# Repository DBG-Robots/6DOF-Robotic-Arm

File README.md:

# 6DOF Robotic Arm

A 6 degree-of-freedom robotic arm built from scratch. The project covers the full hardware and software stack: a custom STM32-based motor controller PCB, 3D-printed mechanical structure, and embedded firmware.

---

## Project Status

| Area | Status |
|---|---|
| Schematic | Complete |
| PCB Layout | In progress |
| STM32CubeMX pin assignment | Complete |
| Firmware | Not started |
| 3D Design | Not started |

---

## Repository Structure

```
.
├── LICENSE
├── PCB/
│   ├── Arm_Controller.kicad_sch       # Top-level schematic
│   ├── MCU.kicad_sch                  # STM32G431CBT6 schematic sheet
│   ├── Drivers.kicad_sch              # TMC2209 driver schematic sheet
│   ├── Power.kicad_sch                # Power supply schematic sheet
│   ├── Connectors.kicad_sch           # Connector schematic sheet
│   ├── Indicator.kicad_sch            # LED indicator schematic sheet
│   ├── Arm_Controller.kicad_pcb       # PCB layout
│   ├── Arm_Controller.kicad_pro       # KiCad project file
│   └── hardware/                      # Datasheets and reference material
└── STM32Cube/
    ├── Core/                          # Generated HAL application code
    ├── Drivers/                       # STM32 HAL and CMSIS drivers
    ├── EWARM/                         # IAR project files
    └── Robot Arm.ioc                  # STM32CubeMX configuration
```

---

## Hardware Overview

### Microcontroller — STM32G431CBT6

The board is centred around an STM32G431CBT6 in LQFP48 packaging, running at 170 MHz via PLL sourced from an 8 MHz external HSE crystal. USB uses the internal HSI48 oscillator via the CK48 mux to hit exactly 48 MHz without pulling the main PLL.

Flash latency is configured to `FLASH_LATENCY_4` as required at 170 MHz. The HAL timebase is moved from SysTick to TIM6 to avoid conflict with the USB stack.

SWD debug is available on PA13 (SWDIO) and PA14 (SWCLK).

### Stepper Motor Drivers — TMC2209

Six TMC2209 drivers handle the six stepper motor axes. Drivers are split into two banks of three, each sharing a UART line for configuration:

- **USART1 (PA9)** — Motors 1–3, half-duplex, 115200 baud
- **USART2 (PB3)** — Motors 4–6, half-duplex, 115200 baud

Up to three drivers share a single UART line using the TMC2209 address selection scheme via MS1/MS2 pins (addresses 0–3).

Each driver exposes a STEP input driven by hardware PWM (TIM2/TIM3 channels), a DIR GPIO, and a shared active-low enable line per bank (TMC_A_ENN, TMC_B_ENN). DIAG outputs from all six drivers are wired to EXTI lines 10–15 on PORTB for simultaneous independent fault interrupts.

Motor output pins (A1, A2, B1, B2 per driver) connect to 5 mm pitch screw terminals for direct stepper wiring.

Sense resistors are 0.11 Ω in 1206 package. Sustained motor current must not exceed 1.5 A per driver to stay within the 0.25 W resistor rating.

The TMC2209 accepts 4.75 V to 29 V on its motor supply. The 24 V rail is protected by a TVS diode clamping at ~29 V to keep transient spikes within this limit, particularly relevant when running from a 6S LiPo (max 25.2 V fully charged).

#### SPREAD Pin Configuration

Each driver has a dedicated 3-way solder jumper (`TMCX_SPREAD`) to select the chopper mode:

| SPREAD state | Mode |
|---|---|
| Pulled LOW (GND) | StealthChop2 — ultra-quiet operation |
| Pulled HIGH (3V3) | SpreadCycle — maximum torque |

Default: pulled HIGH (SpreadCycle). A 100 Ω series resistor is placed between the 3V3 rail and pad 1 of each jumper to limit current in the event of accidental full bridge.

> **Friendly Reminder:** Always have exactly ONE bridge between two pads! Keeping SPREAD floating will result in undefined behaviour and bridging all 3 pads will short GND and +3V3, resulting in a useless piece of green fiberglass. We do not take responsibility for this happening and recommend always testing for a short after resoldering these solder bridges.

### CAN Bus — FDCAN1 with ISO1042DWVR Isolator

CAN communication uses the STM32 FDCAN1 peripheral on PB8 (RX) and PB9 (TX), galvanically isolated via an ISO1042DWVR transceiver. The MCU side runs at 3.3 V; the bus side uses a 5 V isolated supply. Both supply pins carry decoupling capacitors close to the IC.

A 120 Ω termination resistor between CAN_H and CAN_L is present on the bus side, controlled by a solder bridge jumper (JP1). Close JP1 only if this board sits at a physical endpoint of the CAN bus. The default state is open.

> **Note:** JP1 default is OPEN. Exactly two 120 Ω terminations must be present across the entire CAN bus.

The ISO1042 is rated for CAN FD up to 5 Mbps. The board is currently configured for classic CAN. FDCAN timing parameters will need to be recalculated once SYSCLK is confirmed at 170 MHz.

> **TODO:** CAN bus connector footprint is `Connector_Molex:Molex_Pico-Lock_504050-0791_1x07-1MP_P1.50mm_Horizontal`. Exact pinout for the robot-side harness is not yet defined — document and lock this before PCB sign-off.

### Power System

Three 24 V power inputs feed the board via a shared pre-fuse node (`VBAT_IN`), then through a 15 A / 50 V fuse onto the protected `+24V` bus:

- **Robot power distribution board** — dedicated 2-pin connector. Protected by a Schottky diode (MBR1545, SMB package) so no current can ever flow back into the distribution board.
- **Battery** — XT60 female connector on-board, intended for 6S LiPo (22.2 V nominal, 25.2 V max fully charged). Protected by a Schottky diode in the same way.
- **J_PWR24V** — 2-pin 5 mm screw terminal. Accepts a standard 24 V DC supply or any external 24 V source. Also usable as a 24 V output tap. **No diode protection on this connector** — it connects directly to the `VBAT_IN` node ahead of the fuse. Polarity is marked clearly on silkscreen. Reverse polarity here will damage the board.

All three sources meet at `VBAT_IN` before the fuse, so all input current passes through fuse protection regardless of which source is used. Only one power source should be connected at a time.

> **Schottky diode note (MBR1545, D_SMB footprint):** Pin 1 = cathode, pin 2 = anode, pad 3 (thermal tab) = cathode. Pad 3 must be assigned the `VBAT_IN` net in KiCad — it is electrically the cathode and must not be left floating.

#### 24 V Rail Protection

The +24V bus carries decoupling and transient protection split across two locations — one cluster per driver bank — to minimise trace inductance to each group of three TMC2209s:

- A large electrolytic bulk capacitor (1000 µF / 50 V) placed centrally absorbs worst-case transients from all six drivers simultaneously
- Two ceramic capacitors (100 nF / 50 V, 0603) — one per driver bank cluster — handle high-frequency switching noise locally
- Two unidirectional TVS diodes (SMBJ26A) — one per driver bank cluster — clamp transients to protect the TMC2209 drivers, which have a 29 V absolute maximum rating

#### 3.3 V Regulation

Two separate paths supply the 3.3 V rail depending on power source. Both feed through a Schottky diode OR arrangement so neither source can back-feed the other.

**Buck converter (24 V → 3.3 V), used during normal operation:**

Placed in the top-right area of the board, drawing from the +24V bus. The buck converter output is nominally ~3.65 V. With approximately 0.30 V drop across the downstream Schottky diode at typical load, the STM32 VDD rail sits at approximately 3.35 V — within the 2.0 V–3.6 V operating range. The 3.3 V output trace crosses the power plane split boundary on layer 1 to reach the 3V3 plane region under the MCU.

**LDO (USB 5 V → 3.3 V), used during debug/programming only:**

Placed in the bottom-right area alongside the USB-C connector, minimising the VBUS trace length. The LDO output is 3.3 V. With the Schottky drop (~0.30 V at typical load), the STM32 VDD rail sits at approximately 3.0 V — still within the operating range, but marginal. USB power does not supply the motor drivers.

> If exactly 3.3 V is required at the MCU, replace the Schottky diode with an ideal diode circuit, or remove the debug USB power path entirely.

#### 3.3 V Rail Filtering

Given the noisy 24 V environment (6 switching stepper drivers), the 3.3 V rail carries additional filtering beyond a basic dev board:

- A ferrite bead at the rail entry point attenuates noise before it reaches any VDD decoupling
- A bulk reservoir capacitor handles load transients and converter lag
- Three 100 nF ceramics provide per-pin HF decoupling on VDD
- A second, higher-impedance ferrite bead further isolates the VDDA analog supply from VDD
- VDDA carries both a 100 nF and a 1 µF capacitor per ST's reference design
- VREF+ carries a 100 nF decoupling capacitor; a 0 Ω jumper allows VREF+ to be separated from VDDA if needed

### USB

Full-speed USB device on PA11 (DM) and PA12 (DP), clocked from HSI48. Intended for firmware flashing and debug only — does not power the motor drivers. USB-C connector placed bottom-right, adjacent to the LDO.

---

## PCB Layout

### Layer Stack

4-layer board:

| Layer | Use |
|---|---|
| 1 — Top copper | Signal and power routing |
| 2 — GND plane | Unbroken ground reference across the full board |
| 3 — Power plane | Split: 24 V under motor outputs and power section (U-shape), 3V3 under MCU and logic |
| 4 — Bottom copper | Signal routing |

The power plane split boundary runs between the motor-side pads and logic-side pads of each TMC2209 footprint. The GND plane is never split.

### Board Layout

The board follows a U-shaped topology with a central logic section:

- **Top edge** — Motors 4–6: screw terminals facing outward, TMC2209s below with 24 V side facing the edge and logic side facing inward
- **Bottom edge** — Motors 1–3: same orientation mirrored
- **Right-center** — Power input section: XT60 (VBAT), EXTN_PWR connector, J_PWR24V screw terminal, Schottky diodes D1/D2, fuse F1, bulk cap C13, ceramic caps and TVS diodes for each driver bank
- **Top-right** — 24 V → 3.3 V buck converter
- **Bottom-right** — USB-C connector and LDO (5 V → 3.3 V)
- **Center** — STM32G431CBT6, 3.3 V filtering, crystal, decoupling
- **Left edge** — CAN header and isolator (ISO1042DWVR), SWD debug header (J15), expansion headers, LED indicators

### Power Plane Notes

The 24 V plane covers the outer half of the board in a U-shape (top driver bank, power section, bottom driver bank). The 3.3 V plane occupies the inner-right region under the STM32, CAN isolator, and logic components. A copper-free gap separates the two regions; a single GND via stitch bridges them at one point to maintain a common ground reference without creating a loop.

All TMC2209 footprints are oriented so motor output pads (A1, A2, B1, B2) sit over the 24 V plane and logic pads (STEP, DIR, UART, DIAG) sit over the 3.3 V plane. The plane split line runs through the gap between these pad clusters on each driver.

---

## Pin Assignment

### STEP Outputs (Hardware PWM)

| Pin | Label | Timer Channel |
|---|---|---|
| PA0 | TMC1_STEP | TIM2_CH1 |
| PA1 | TMC2_STEP | TIM2_CH2 |
| PA6 | TMC3_STEP | TIM3_CH1 |
| PA7 | TMC4_STEP | TIM3_CH2 |
| PB0 | TMC5_STEP | TIM3_CH3 |
| PB1 | TMC6_STEP | TIM3_CH4 |

TIM2 and TIM3 run independently, allowing different step rates per motor bank.

### DIR Outputs (GPIO)

| Pin | Label |
|---|---|
| PA3 | M1_DIR |
| PA4 | M2_DIR |
| PA5 | M3_DIR |
| PB4 | M4_DIR |
| PB5 | M5_DIR |
| PB6 | M6_DIR |

Grouped by port to allow efficient single-register writes.

### Enable Outputs (Active LOW)

| Pin | Label | Controls |
|---|---|---|
| PA10 | TMC_A_ENN | Motors 1–3 |
| PA15 | TMC_B_ENN | Motors 4–6 |

Pulling both low implements a hardware e-stop across all six axes.

### DIAG Inputs (EXTI)

| Pin | Label | EXTI Line |
|---|---|---|
| PB10 | TMC1_DIAG | EXTI10 |
| PB11 | TMC2_DIAG | EXTI11 |
| PB12 | TMC3_DIAG | EXTI12 |
| PB13 | TMC4_DIAG | EXTI13 |
| PB14 | TMC5_DIAG | EXTI14 |
| PB15 | TMC6_DIAG | EXTI15 |

All DIAG lines sit on unique EXTI lines, so all six can fire simultaneously without arbitration. DIAG is driven HIGH by the TMC2209 on stall or fault detection.

### Indicators

| LED | Pin | Resistor | Color |
|---|---|---|---|
| STATUS_LED | PC13 | 1 kΩ | Red |
| POWER_LED | +3V3 (always-on) | 1.1 kΩ | Green |
| ACTIVITY_LED | PA8 | 390 Ω | Blue |

### Expansion Headers

| Pin | Use |
|---|---|
| PA2 | 3-pin 2.54 mm header (BTN/FAN/Thermistor) |
| PB2 | 3-pin 2.54 mm header (BTN/FAN) |
| PB7 | TIM4_CH2 — recommended for PWM fan control |

Headers are 3-pin 2.54 mm (GND / Signal / 3V3) with 10 kΩ pullup on the signal line for a defined state when unplugged.

PA2 is additionally suitable as a thermistor input (ADC) — the 10 kΩ pullup acts as the upper half of a voltage divider. Standard 10 kΩ NTC thermistors connect between the PA2 signal pad and GND.

---

## BOOT0 / PB8 — nBOOT_SEL Configuration

PB8 is shared between the FDCAN1_RX function and BOOT0. To free PB8 for CAN use permanently, the option byte **nBOOT_SEL = 1** must be programmed via STM32CubeProgrammer at first flash. This redirects boot mode selection away from the physical BOOT0 pin to the nBOOT0 option bit, which is set to 1 (normal boot from flash).

No physical BOOT or RESET button is fitted. NRST is accessible via pin 12 of the SWD header.

A test pad (TP_PB8) is placed on the PCB for two purposes:

1. Probing the CAN receive signal during bring-up.
2. Emergency bootloader recovery on boards where nBOOT_SEL was not programmed correctly — hold TP_PB8 HIGH at power-on to force the ROM bootloader via USB DFU.

---

## SWD Debug Header — J15

- Connector: 2×7 pin, 1.27 mm pitch, vertical through-hole
- KiCad footprint: `Connector_PinHeader_1.27mm:PinHeader_2x07_P1.27mm_Vertical`
- Pinout: STDC14 per ST UM2448 Table 6
- Preferred part: Samtec FTSH-107-01-L-DV-K-A (adds alignment shroud; any 2×7 1.27 mm header is electrically equivalent)
- Recommended debugger: **STLINK-V3MINIE** (ships with STDC14 ribbon cable)

| Pin | Signal |
|---|---|
| 1, 2 | Reserved — NC |
| 3 | T_VCC → +3V3 |
| 4 | SWDIO → PA13 |
| 5, 7 | GND |
| 6 | SWCLK → PA14 |
| 8 | SWO → NC (PB3 occupied by USART2) |
| 9 | NC |
| 10 | NC |
| 11 | GNDDetect → GND |
| 12 | NRST |
| 13, 14 | VCP RX/TX → NC |

---

## Test Points

All test points use 2.0 mm round pads for power rails and 1.0 mm round pads for signals, compatible with flying probe and pogo pin fixtures.

| Signal | Notes |
|---|---|
| GND | Power |
| +3V3 | Power |
| +24V | Power |
| VBUS | Power |
| CC1 | USB |
| CC2 | USB |
| TMC1–6 DIAG | One pad per driver |
| TMC1–6 INDEX | One pad per driver |
| TP_PB8 / BOOT0 | 1.5 mm round pad — CAN RX probe point and bootloader recovery |
| VDDA | Analog supply, after the VDDA ferrite bead |
| VREF+ | ADC reference rail |
| SWDIO | Debug |
| SWDCLK | Debug |
| NRST | Reset |
| CAN_H | Bus signal |
| CAN_L | Bus signal |
| CAN_GND | Bus ground reference |
| CAN_UART_TX | ISO1042 MCU-side TX |
| CAN_UART_RX | ISO1042 MCU-side RX |
| TMC_UART1 | USART1 half-duplex line (motors 1–3) |
| TMC_UART2 | USART2 half-duplex line (motors 4–6) |
| SW_NODE | Buck converter switching node — for scope noise analysis during bring-up |

---

## Known Issues and Open Items

- CAN connector pinout (Molex Pico-Lock 504050-0791) not yet defined for the robot-side harness.
- Connector for robot power distribution board not yet selected — footprint TBD.
- FDCAN timing parameters need recalculation after SYSCLK is confirmed at 170 MHz.
- PCB layout in progress — component placement largely complete, routing not yet started.
- Diode footprints (D1, D2): pad 3 (thermal tab) must be assigned `VBAT_IN` net in KiCad before routing.
- Buck converter and LDO placement pending final placement confirmation.
- Firmware not started.
- 3D mechanical design not started.

---

## Authorship

### 6DOF Robotic Arm — DBG-Robots

**Merlin Ortner**  
**Repository Owner & Principal Maintainer**  
Original author of this repository and responsible for long-term maintenance, development, and stewardship.  
Contact: ortnermerlin@gmail.com

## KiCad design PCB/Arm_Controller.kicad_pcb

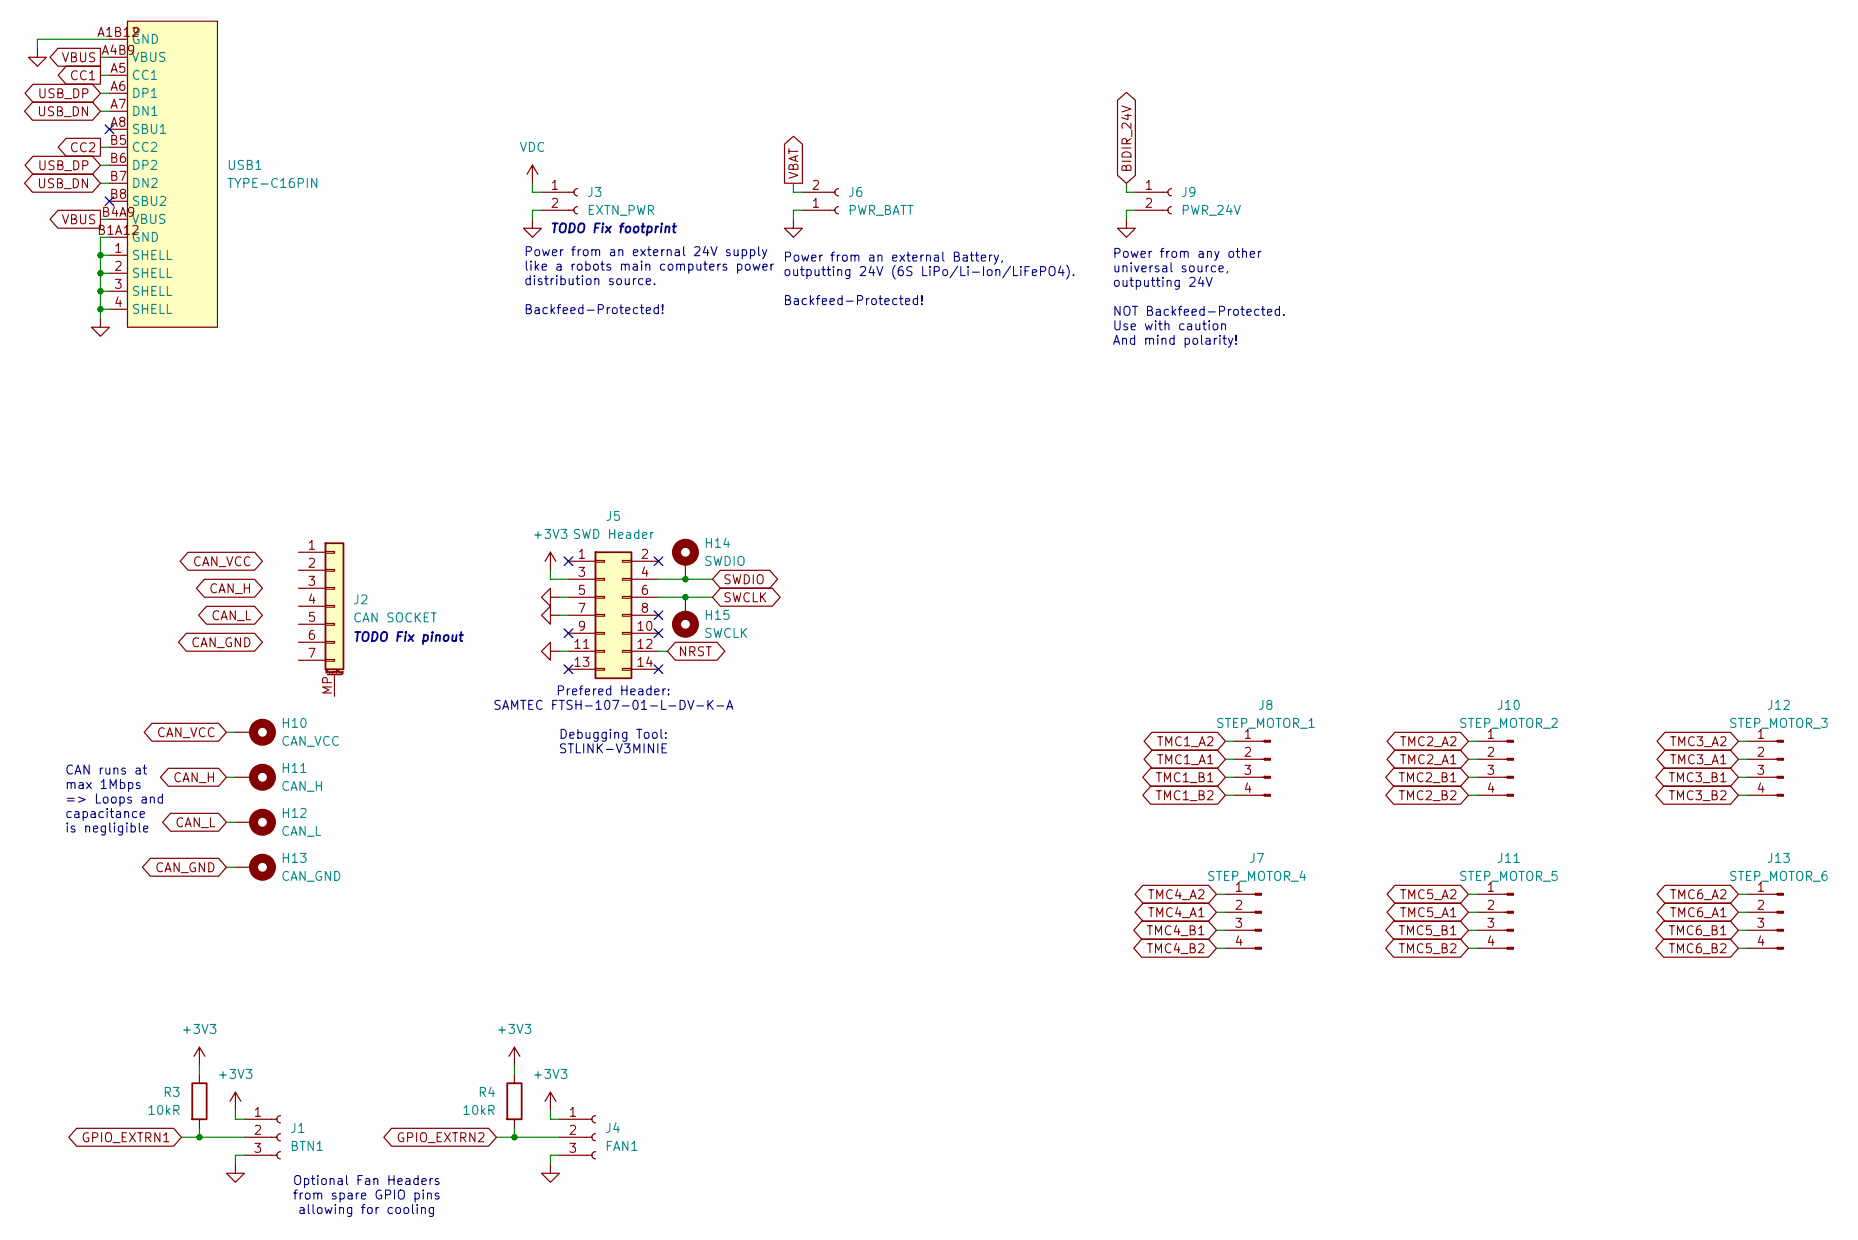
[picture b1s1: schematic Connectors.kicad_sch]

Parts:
H10: CAN_VCC; TestPoint_Pad_D2.0mm
H11: CAN_H; TestPoint_Pad_D1.0mm
H12: CAN_L; TestPoint_Pad_D1.0mm
H13: CAN_GND; TestPoint_Pad_D2.0mm
H14: SWDIO; TestPoint_Pad_D1.0mm
H15: SWCLK; TestPoint_Pad_D1.0mm
J1: BTN1; FanPinHeader_1x03_P2.54mm_Vertical
J2: CAN SOCKET; Molex_Pico-Lock_504050-0791_1x07-1MP_P1.50mm_Horizontal
J3: EXTN_PWR; Molex_SPOX_5267-02A_1x02_P2.50mm_Vertical
J4: FAN1; FanPinHeader_1x03_P2.54mm_Vertical
J5: SWD Header; PinHeader_2x07_P1.27mm_Vertical
J6: PWR_BATT; AMASS_XT60PW-F_1x02_P7.20mm_Horizontal
J7: STEP_MOTOR_4; TerminalBlock_Phoenix_MKDS-1,5-4-5.08_1x04_P5.08mm_Horizont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
J8: STEP_MOTOR_1; TerminalBlock_Phoenix_MKDS-1,5-4-5.08_1x04_P5.08mm_Horizont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
J9: PWR_24V; TerminalBlock_MaiXu_MX126-5.0-02P_1x02_P5.00mm
J10: STEP_MOTOR_2; TerminalBlock_Phoenix_MKDS-1,5-4-5.08_1x04_P5.08mm_Horizont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
J11: STEP_MOTOR_5; TerminalBlock_Phoenix_MKDS-1,5-4-5.08_1x04_P5.08mm_Horizont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
J12: STEP_MOTOR_3; TerminalBlock_Phoenix_MKDS-1,5-4-5.08_1x04_P5.08mm_Horizont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
J13: STEP_MOTOR_6; TerminalBlock_Phoenix_MKDS-1,5-4-5.08_1x04_P5.08mm_Horizont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
R3, R4: 10kR; R_0402_1005Metric
USB1: TYPE-C16PIN; USB-C-SMD_TYPE-C16PIN; MPN TYPE-C16PIN; LCSC Part C393939

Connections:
+3V3: J1.1, J4.1, J5.3, R3.1, R4.1; also elsewhere on the board
BIDIR_24V: J9.1; also elsewhere on the board
CAN_GND: H13.1 (1_1); also elsewhere on the board
CAN_H: H11.1 (1_1); also elsewhere on the board
CAN_L: H12.1 (1_1); also elsewhere on the board
CAN_VCC: H10.1 (1_1); also elsewhere on the board
CC1: USB1.A5 (CC1); also elsewhere on the board
CC2: USB1.B5 (CC2); also elsewhere on the board
GND: J1.3, J3.2, J4.3, J5.5, J5.7, J5.11, J6.1, J9.2, USB1.1 (SHELL), USB1.2 (SHELL), USB1.3 (SHELL), USB1.4 (SHELL), USB1.A1B12 (GND), USB1.B1A12 (GND); also elsewhere on the board
GPIO_EXTRN1: J1.2, R3.2; also elsewhere on the board
GPIO_EXTRN2: J4.2, R4.2; also elsewhere on the board
NRST: J5.12; also elsewhere on the board
SWCLK: H15.1 (1_1), J5.6; also elsewhere on the board
SWDIO: H14.1 (1_1), J5.4; also elsewhere on the board
TMC1_A1: J8.2; also elsewhere on the board
TMC1_A2: J8.1; also elsewhere on the board
TMC1_B1: J8.3; also elsewhere on the board
TMC1_B2: J8.4; also elsewhere on the board
TMC2_A1: J10.2; also elsewhere on the board
TMC2_A2: J10.1; also elsewhere on the board
TMC2_B1: J10.3; also elsewhere on the board
TMC2_B2: J10.4; also elsewhere on the board
TMC3_A1: J12.2; also elsewhere on the board
TMC3_A2: J12.1; also elsewhere on the board
TMC3_B1: J12.3; also elsewhere on the board
TMC3_B2: J12.4; also elsewhere on the board
TMC4_A1: J7.2; also elsewhere on the board
TMC4_A2: J7.1; also elsewhere on the board
TMC4_B1: J7.3; also elsewhere on the board
TMC4_B2: J7.4; also elsewhere on the board
TMC5_A1: J11.2; also elsewhere on the board
TMC5_A2: J11.1; also elsewhere on the board
TMC5_B1: J11.3; also elsewhere on the board
TMC5_B2: J11.4; also elsewhere on the board
TMC6_A1: J13.2; also elsewhere on the board
TMC6_A2: J13.1; also elsewhere on the board
TMC6_B1: J13.3; also elsewhere on the board
TMC6_B2: J13.4; also elsewhere on the board
USB_DN: USB1.A7 (DN1), USB1.B7 (DN2); also elsewhere on the board
USB_DP: USB1.A6 (DP1), USB1.B6 (DP2); also elsewhere on the board
VBAT: J6.2; also elsewhere on the board
VBUS: USB1.A4B9 (VBUS), USB1.B4A9 (VBUS); also elsewhere on the board
VDC: J3.1; also elsewhere on the board

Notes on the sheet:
TODO Fix footprint
Power from an external 24V supply like a robots main computers power distribution source. Backfeed-Protected!
Power from an external Battery, outputting 24V (6S LiPo/Li-Ion/LiFePO4). Backfeed-Protected!
CAN runs at max 1Mbps => Loops and capacitance is negligible
TODO Fix pinout
Prefered Header: SAMTEC FTSH-107-01-L-DV-K-A Debugging Tool: STLINK-V3MINIE
Optional Fan Headers from spare GPIO pins allowing for cooling
Power from any other universal source, outputting 24V NOT Backfeed-Protected. Use with caution And mind polarity!

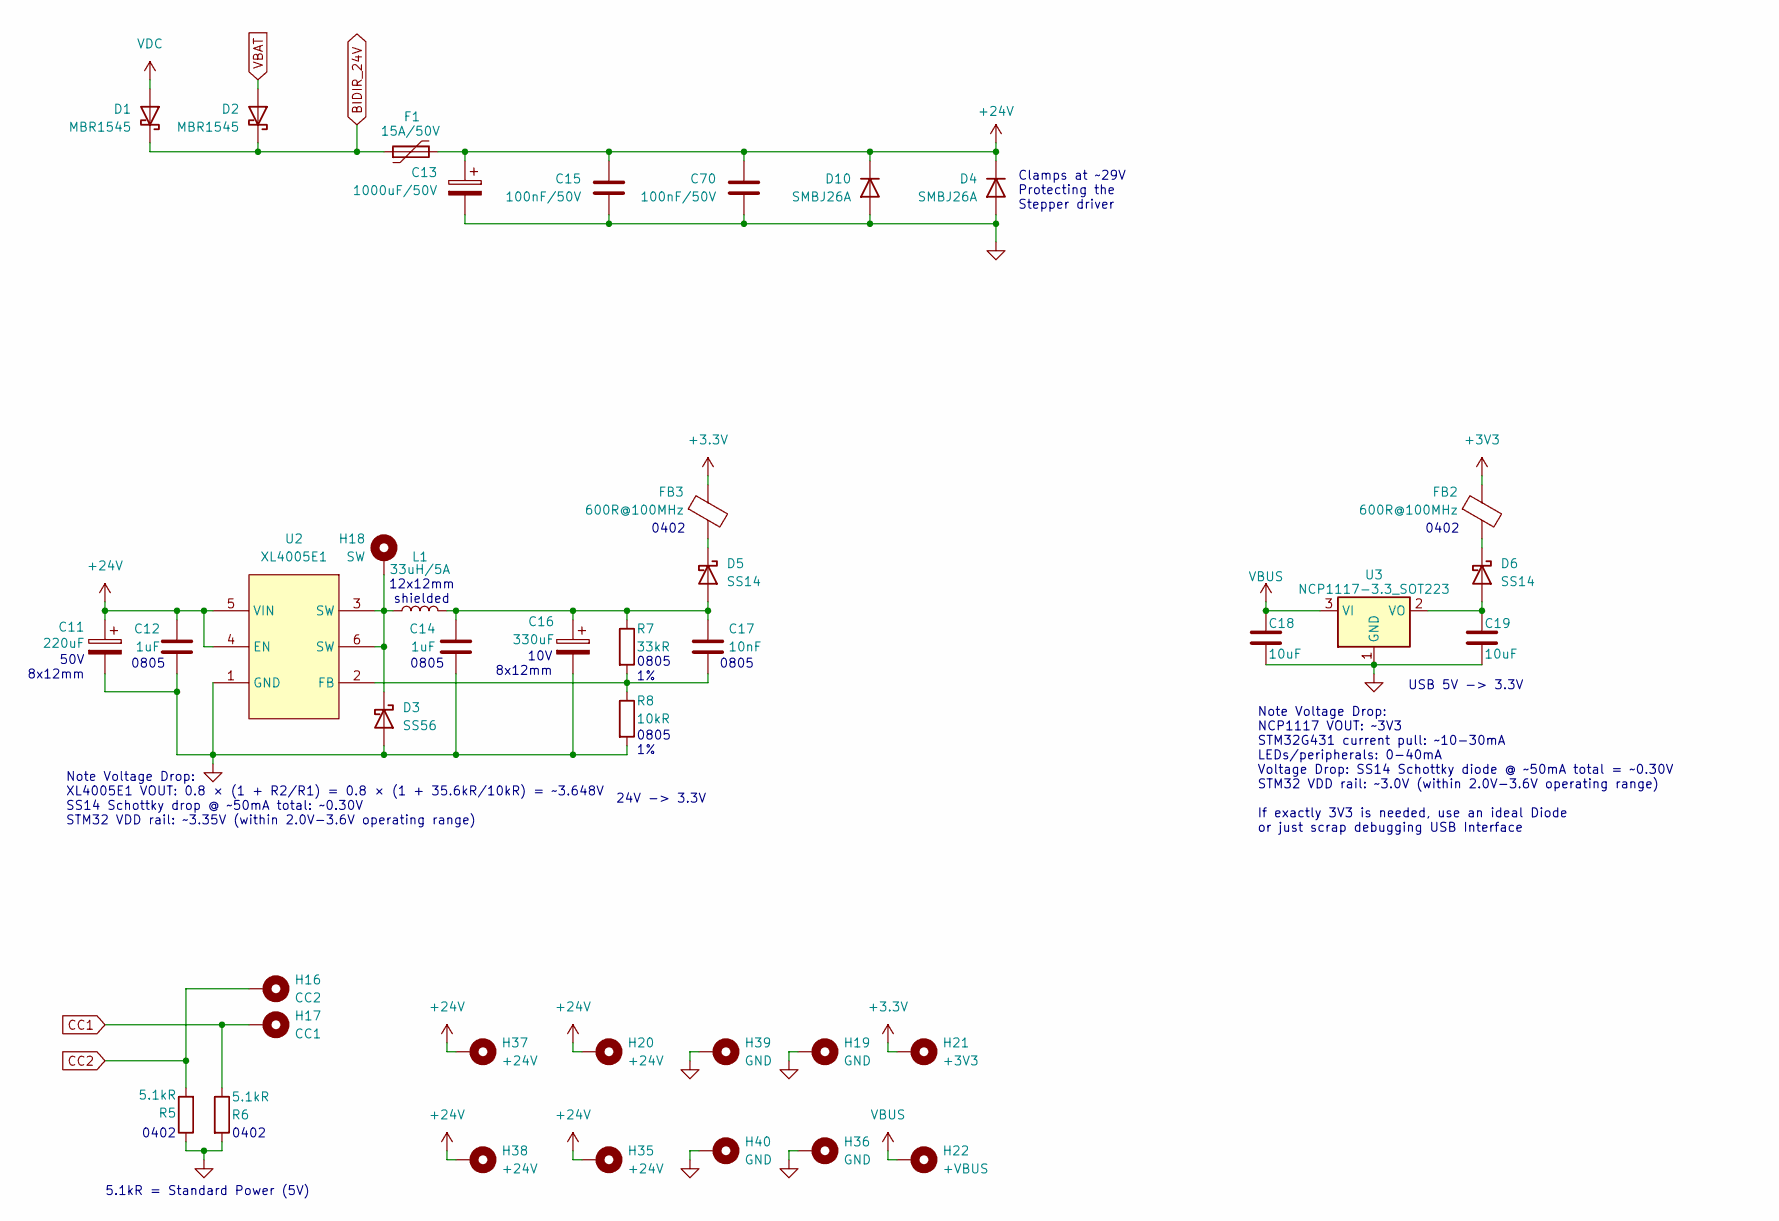
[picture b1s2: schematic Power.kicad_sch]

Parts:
C11: 220uF; CP_Radial_D8.0mm_P3.50mm
C12, C14: 1uF; C_0805_2012Metric
C13: 1000uF/50V; CP_Radial_D10.0mm_P5.00mm
C15, C70: 100nF/50V; C_0603_1608Metric
C16: 330uF; CP_Elec_8x10
C17: 10nF; C_0805_2012Metric
C18, C19: 10uF; C_0805_2012Metric
D1, D2: MBR1545; TO-263-2
D3: SS56; D_SMA
D4, D10: SMBJ26A; D_SMB
D5, D6: SS14; D_SMA
F1: 15A/50V; Fuseholder_Blade_ATO_Littelfuse_Pudenz_2_Pin
FB2, FB3: 600R@100MHz; L_0603_1608Metric
H16: CC2; TestPoint_Pad_D1.0mm
H17: CC1; TestPoint_Pad_D1.0mm
H18: SW; TestPoint_Pad_D1.0mm
H19, H36, H39, H40: GND; TestPoint_Pad_D2.0mm
H20, H35, H37, H38: +24V; TestPoint_Pad_D2.0mm
H21: +3V3; TestPoint_Pad_D2.0mm
H22: +VBUS; TestPoint_Pad_D2.0mm
L1: 33uH/5A; L_Bourns_SRR1260
R5, R6: 5.1kR; R_0402_1005Metric
R7: 33kR; R_0805_2012Metric
R8: 10kR; R_0805_2012Metric
U2: XL4005E1; TO-263-5_L10.2-W9.2-P1.70-TL; MPN XL4005E1; LCSC Part C73332
U3: NCP1117-3.3_SOT223; SOT-223-3_TabPin2

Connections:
+3.3V: FB3.1, H21.1 (1_1); also elsewhere on the board
+3V3: FB2.1; also elsewhere on the board
+24V: C11.1, C12.1, C13.1, C15.1, C70.1, D4.1 (K), D10.1 (K), F1.2, H20.1 (1_1), H35.1 (1_1), H37.1 (1_1), H38.1 (1_1), U2.4 (EN), U2.5 (VIN); also elsewhere on the board
BIDIR_24V: D1.1 (K), D2.1 (K), F1.1; also elsewhere on the board
CC1: H17.1 (1_1), R6.1; also elsewhere on the board
CC2: H16.1 (1_1), R5.2; also elsewhere on the board
GND: C11.2, C12.2, C13.2, C14.2, C15.2, C16.2, C18.2, C19.2, C70.2, D3.2 (A), D4.2 (A), D10.2 (A), H19.1 (1_1), H36.1 (1_1), H39.1 (1_1), H40.1 (1_1), R5.1, R6.2, R8.2, U2.1 (GND), U3.1 (GND); also elsewhere on the board
unnamed: D3.1 (K), H18.1 (1_1), L1.1, U2.3 (SW), U2.6 (SW)
unnamed: C14.1, C16.1, C17.1, D5.2 (A), L1.2, R7.1
unnamed: D5.1 (K), FB3.2
unnamed: C19.1, D6.2 (A), U3.2 (VO)
unnamed: D6.1 (K), FB2.2
unnamed: C17.2, R7.2, R8.1, U2.2 (FB)
VBAT: D2.2 (A); also elsewhere on the board
VBUS: C18.1, H22.1 (1_1), U3.3 (VI); also elsewhere on the board
VDC: D1.2 (A); also elsewhere on the board

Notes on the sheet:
0805
0805 1%
Clamps at ~29V Protecting the Stepper driver
10V 8x12mm
Note Voltage Drop: XL4005E1 VOUT: 0.8 × (1 + R2/R1) = 0.8 × (1 + 35.6kR/10kR) = ~3.648V SS14 Schottky drop @ ~50mA total: ~0.30V STM32 VDD rail: ~3.35V (within 2.0V-3.6V operating range)
USB 5V -> 3.3V
24V -> 3.3V
Note Voltage Drop: NCP1117 VOUT: ~3V3 STM32G431 current pull: ~10-30mA LEDs/peripherals: 0-40mA Voltage Drop: SS14 Schottky diode @ ~50mA total = ~0.30V STM32 VDD rail: ~3.0V (within 2.0V-3.6V operating range) If exactly 3V3 is needed, use an ideal Diode or just scrap debugging USB Interface
50V 8x12mm
5.1kR = Standard Power (5V)
0402
12x12mm shielded

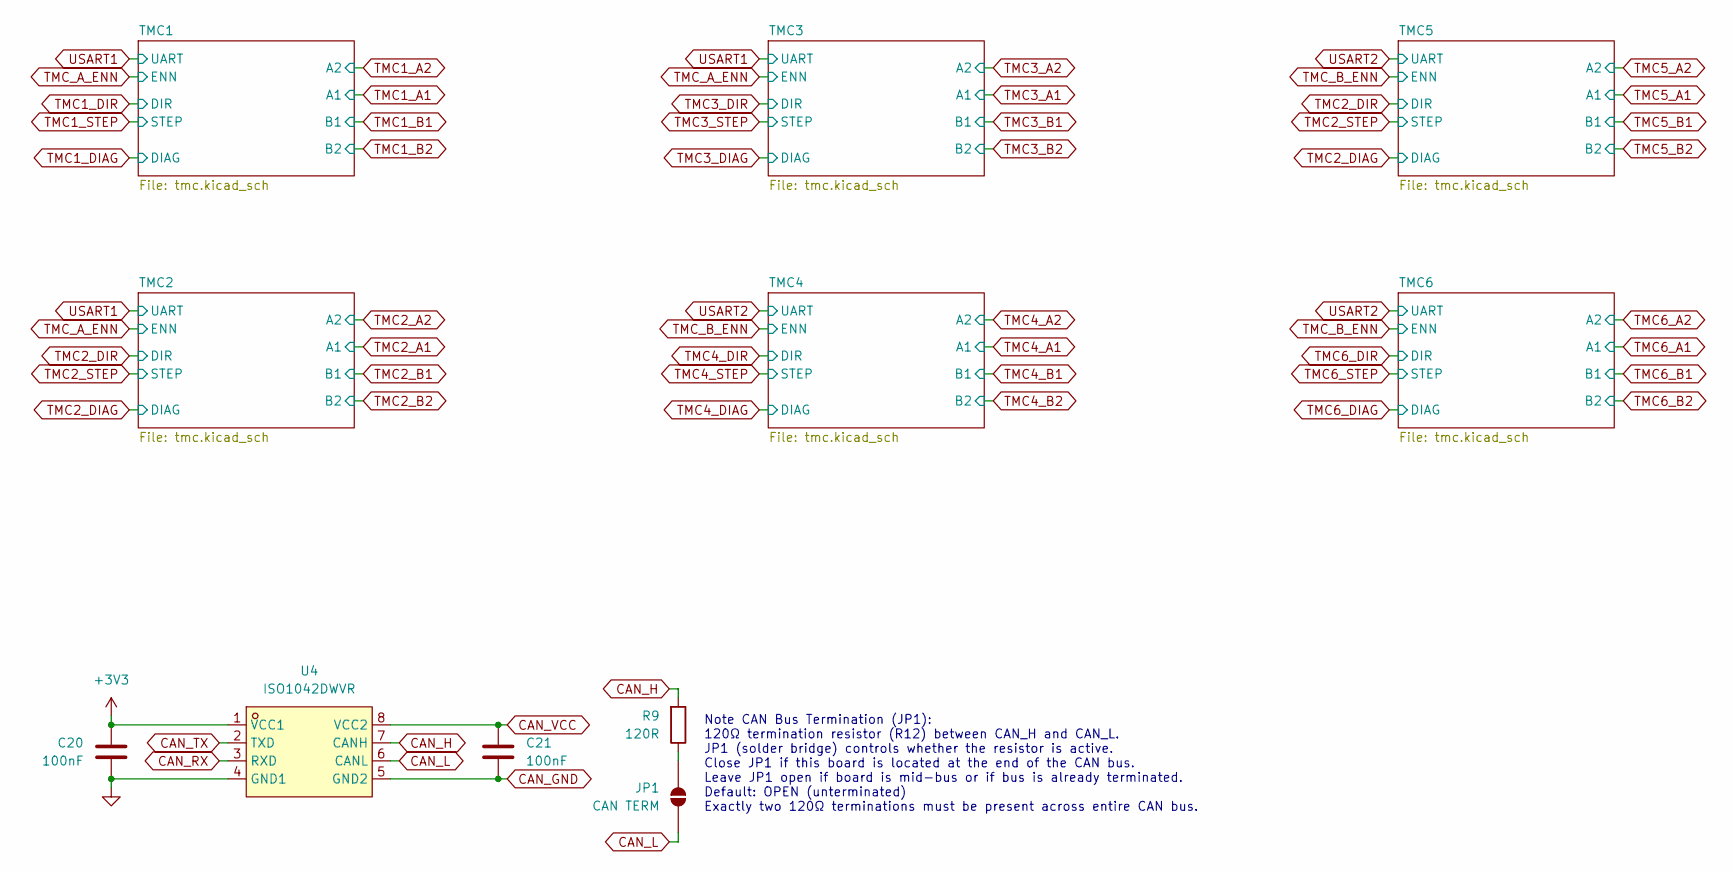
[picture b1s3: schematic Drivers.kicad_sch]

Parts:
C20, C21: 100nF; C_0402_1005Metric
JP1: CAN TERM; SolderJumper-2_P1.3mm_Open_RoundedPad1.0x1.5mm
R9: 120R; R_0402_1005Metric
U4: ISO1042DWVR; SOIC-8_L7.5-W5.9-P1.27-LS11.5-BL; MPN ISO1042DWVR; LCSC Part C2671714

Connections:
+3V3: C20.1, U4.1 (VCC1); also elsewhere on the board
CAN_GND: C21.2, U4.5 (GND2); also elsewhere on the board
CAN_H: R9.2, U4.7 (CANH); also elsewhere on the board
CAN_L: JP1.1 (A), U4.6 (CANL); also elsewhere on the board
CAN_RX: U4.3 (RXD); also elsewhere on the board
CAN_TX: U4.2 (TXD); also elsewhere on the board
CAN_VCC: C21.1, U4.8 (VCC2); also elsewhere on the board
GND: C20.2, U4.4 (GND1); also elsewhere on the board
unnamed: JP1.2 (B), R9.1

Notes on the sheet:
Note CAN Bus Termination (JP1): 120Ω termination resistor (R12) between CAN_H and CAN_L. JP1 (solder bridge) controls whether the resistor is active. Close JP1 if this board is located at the end of the CAN bus. Leave JP1 open if board is mid-bus or if bus is already terminated. Default: OPEN (unte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

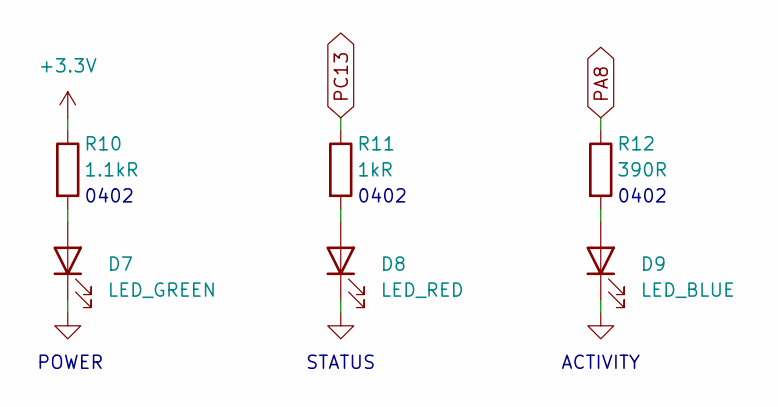
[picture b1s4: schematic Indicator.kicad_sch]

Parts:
D7: LED_GREEN; LED_0603_1608Metric
D8: LED_RED; LED_0603_1608Metric
D9: LED_BLUE; LED_0603_1608Metric
R10: 1.1kR; R_0402_1005Metric
R11: 1kR; R_0402_1005Metric
R12: 390R; R_0402_1005Metric

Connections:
+3.3V: R10.1; also elsewhere on the board
GND: D7.1 (K), D8.1 (K), D9.1 (K); also elsewhere on the board
unnamed: D7.2 (A), R10.2
unnamed: D8.2 (A), R11.2
unnamed: D9.2 (A), R12.2
PA8: R12.1; also elsewhere on the board
PC13: R11.1; also elsewhere on the board

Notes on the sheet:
POWER
0402
STATUS
ACTIVITY

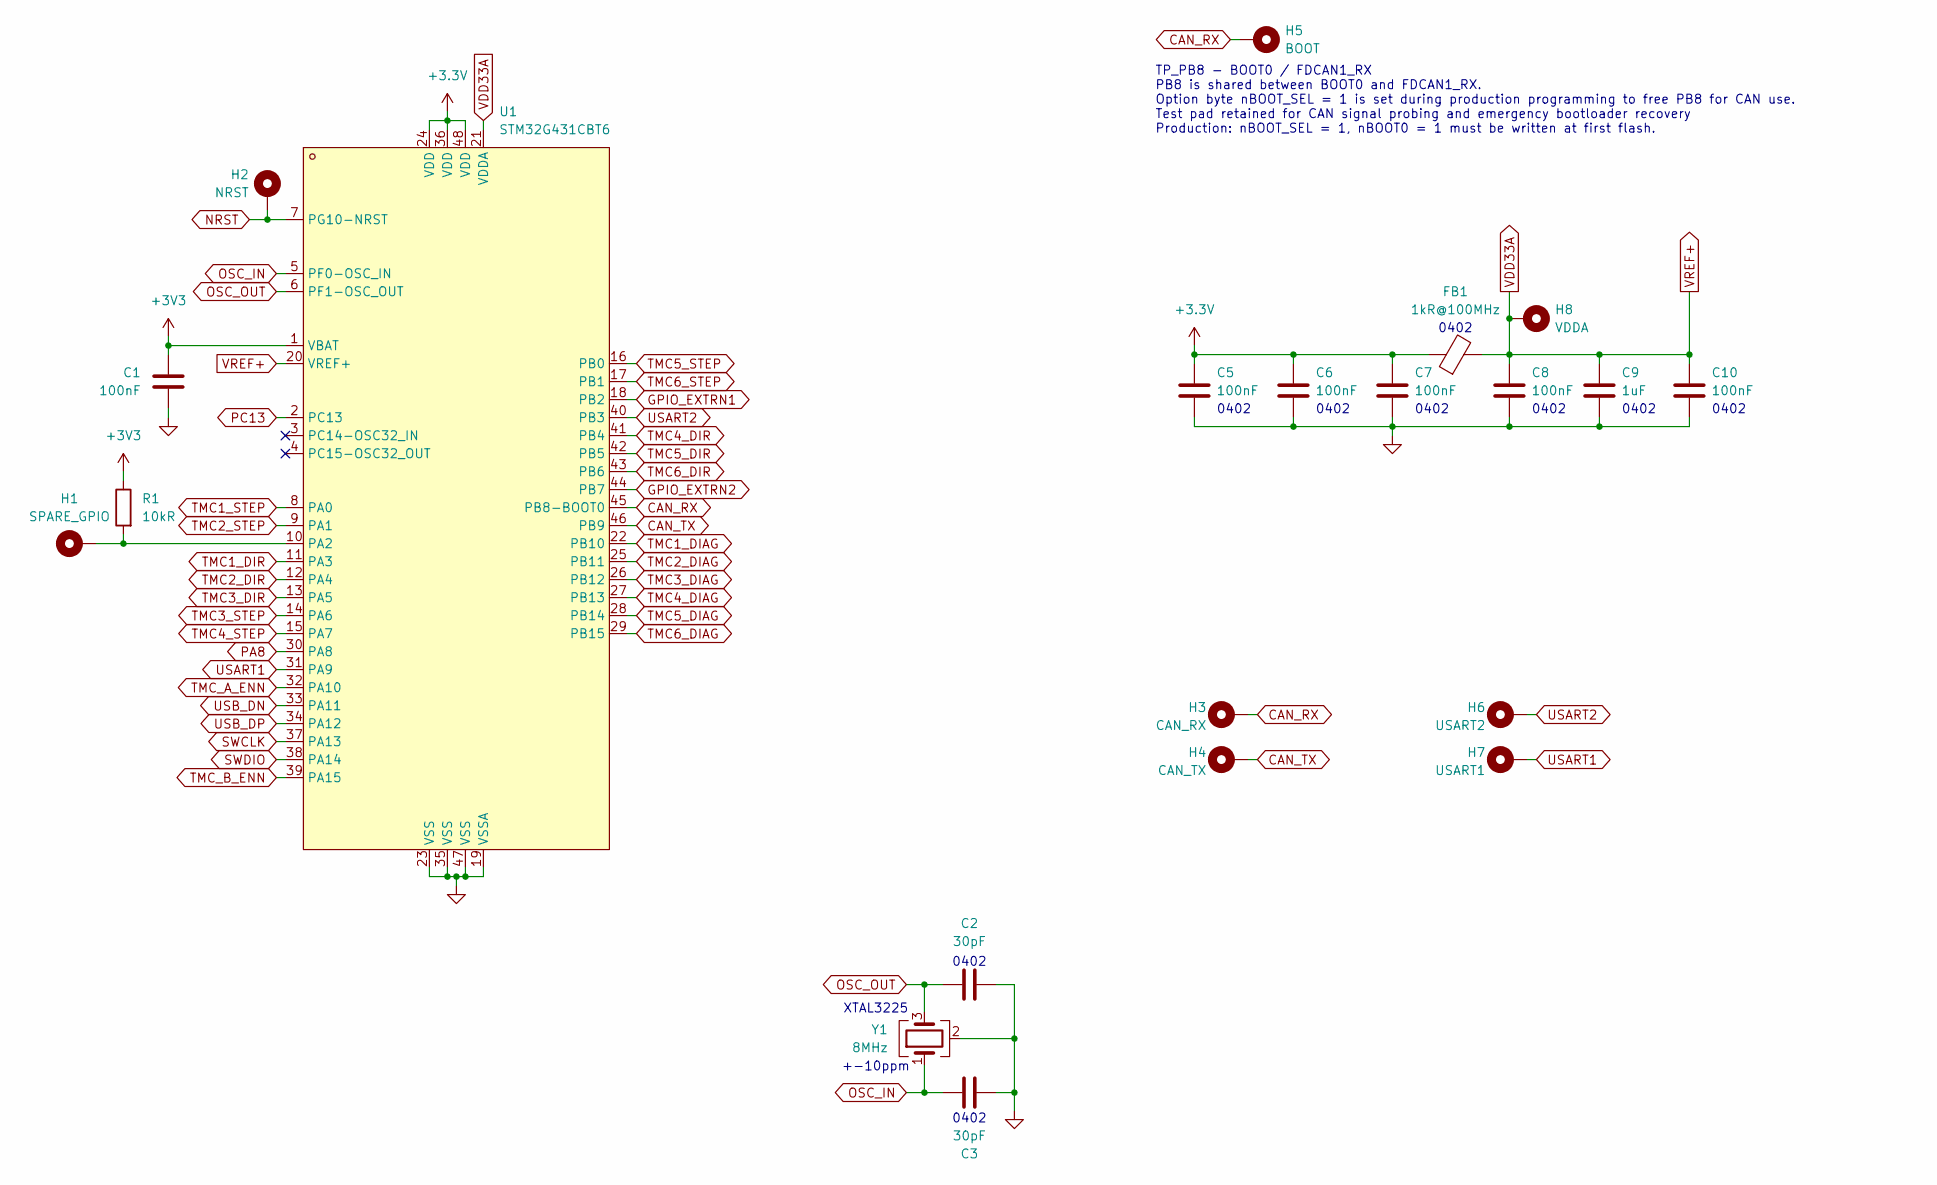
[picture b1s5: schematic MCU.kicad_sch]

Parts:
C1, C5, C6, C7, C8, C10: 100nF; C_0402_1005Metric
C2, C3: 30pF; C_0402_1005Metric
C9: 1uF; C_0402_1005Metric
FB1: 1kR@100MHz; L_0402_1005Metric
H1: SPARE_GPIO; TestPoint_Pad_D1.0mm
H2: NRST; TestPoint_Pad_D1.0mm
H3: CAN_RX; TestPoint_Pad_D1.0mm
H4: CAN_TX; TestPoint_Pad_D1.0mm
H5: BOOT; TestPoint_Pad_D1.0mm
H6: USART2; TestPoint_Pad_D1.0mm
H7: USART1; TestPoint_Pad_D1.0mm
H8: VDDA; TestPoint_Pad_D2.0mm
R1: 10kR; R_0402_1005Metric
U1: STM32G431CBT6; LQFP-48_L7.0-W7.0-P0.50-LS9.0-BL; MPN STM32G431CBT6; LCSC Part C529355
Y1: 8MHz; Crystal_SMD_3225-4Pin_3.2x2.5mm

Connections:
+3.3V: C5.1, C6.1, C7.1, FB1.1, U1.24 (VDD), U1.36 (VDD), U1.48 (VDD); also elsewhere on the board
+3V3: C1.1, R1.1, U1.1 (VBAT); also elsewhere on the board
CAN_RX: H3.1 (1_1), H5.1 (1_1), U1.45 (PB8-BOOT0); also elsewhere on the board
CAN_TX: H4.1 (1_1), U1.46 (PB9); also elsewhere on the board
GND: C1.2, C2.1, C3.2, C5.2, C6.2, C7.2, C8.2, C9.2, C10.2, U1.19 (VSSA), U1.23 (VSS), U1.35 (VSS), U1.47 (VSS), Y1.2 (G), Y1.4 (G); also elsewhere on the board
GPIO_EXTRN1: U1.18 (PB2); also elsewhere on the board
GPIO_EXTRN2: U1.44 (PB7); also elsewhere on the board
NRST: H2.1 (1_1), U1.7 (PG10-NRST); also elsewhere on the board
unnamed: H1.1 (1_1), R1.2, U1.10 (PA2)
OSC_IN: C3.1, U1.5 (PF0-OSC_IN), Y1.1
OSC_OUT: C2.2, U1.6 (PF1-OSC_OUT), Y1.3
PA8: U1.30 (PA8); also elsewhere on the board
PC13: U1.2 (PC13); also elsewhere on the board
SWCLK: U1.37 (PA13); also elsewhere on the board
SWDIO: U1.38 (PA14); also elsewhere on the board
TMC1_DIAG: U1.22 (PB10); also elsewhere on the board
TMC1_DIR: U1.11 (PA3); also elsewhere on the board
TMC1_STEP: U1.8 (PA0); also elsewhere on the board
TMC2_DIAG: U1.25 (PB11); also elsewhere on the board
TMC2_DIR: U1.12 (PA4); also elsewhere on the board
TMC2_STEP: U1.9 (PA1); also elsewhere on the board
TMC3_DIAG: U1.26 (PB12); also elsewhere on the board
TMC3_DIR: U1.13 (PA5); also elsewhere on the board
TMC3_STEP: U1.14 (PA6); also elsewhere on the board
TMC4_DIAG: U1.27 (PB13); also elsewhere on the board
TMC4_DIR: U1.41 (PB4); also elsewhere on the board
TMC4_STEP: U1.15 (PA7); also elsewhere on the board
TMC5_DIAG: U1.28 (PB14)
TMC5_DIR: U1.42 (PB5)
TMC5_STEP: U1.16 (PB0)
TMC6_DIAG: U1.29 (PB15); also elsewhere on the board
TMC6_DIR: U1.43 (PB6); also elsewhere on the board
TMC6_STEP: U1.17 (PB1); also elsewhere on the board
TMC_A_ENN: U1.32 (PA10); also elsewhere on the board
TMC_B_ENN: U1.39 (PA15); also elsewhere on the board
USART1: H7.1 (1_1), U1.31 (PA9); also elsewhere on the board
USART2: H6.1 (1_1), U1.40 (PB3); also elsewhere on the board
USB_DN: U1.33 (PA11); also elsewhere on the board
USB_DP: U1.34 (PA12); also elsewhere on the board
VDD33A: C8.1, C9.1, C10.1, FB1.2, H8.1 (1_1), U1.20 (VREF+), U1.21 (VDDA)

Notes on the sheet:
0402
XTAL3225 +-10ppm
TP_PB8 - BOOT0 / FDCAN1_RX PB8 is shared between BOOT0 and FDCAN1_RX. Option byte nBOOT_SEL = 1 is set during production programming to free PB8 for CAN use. Test pad retained for CAN signal probing and emergency bootloader recovery Production: nBOOT_SEL = 1, nBOOT0 = 1 must be written at first fla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
